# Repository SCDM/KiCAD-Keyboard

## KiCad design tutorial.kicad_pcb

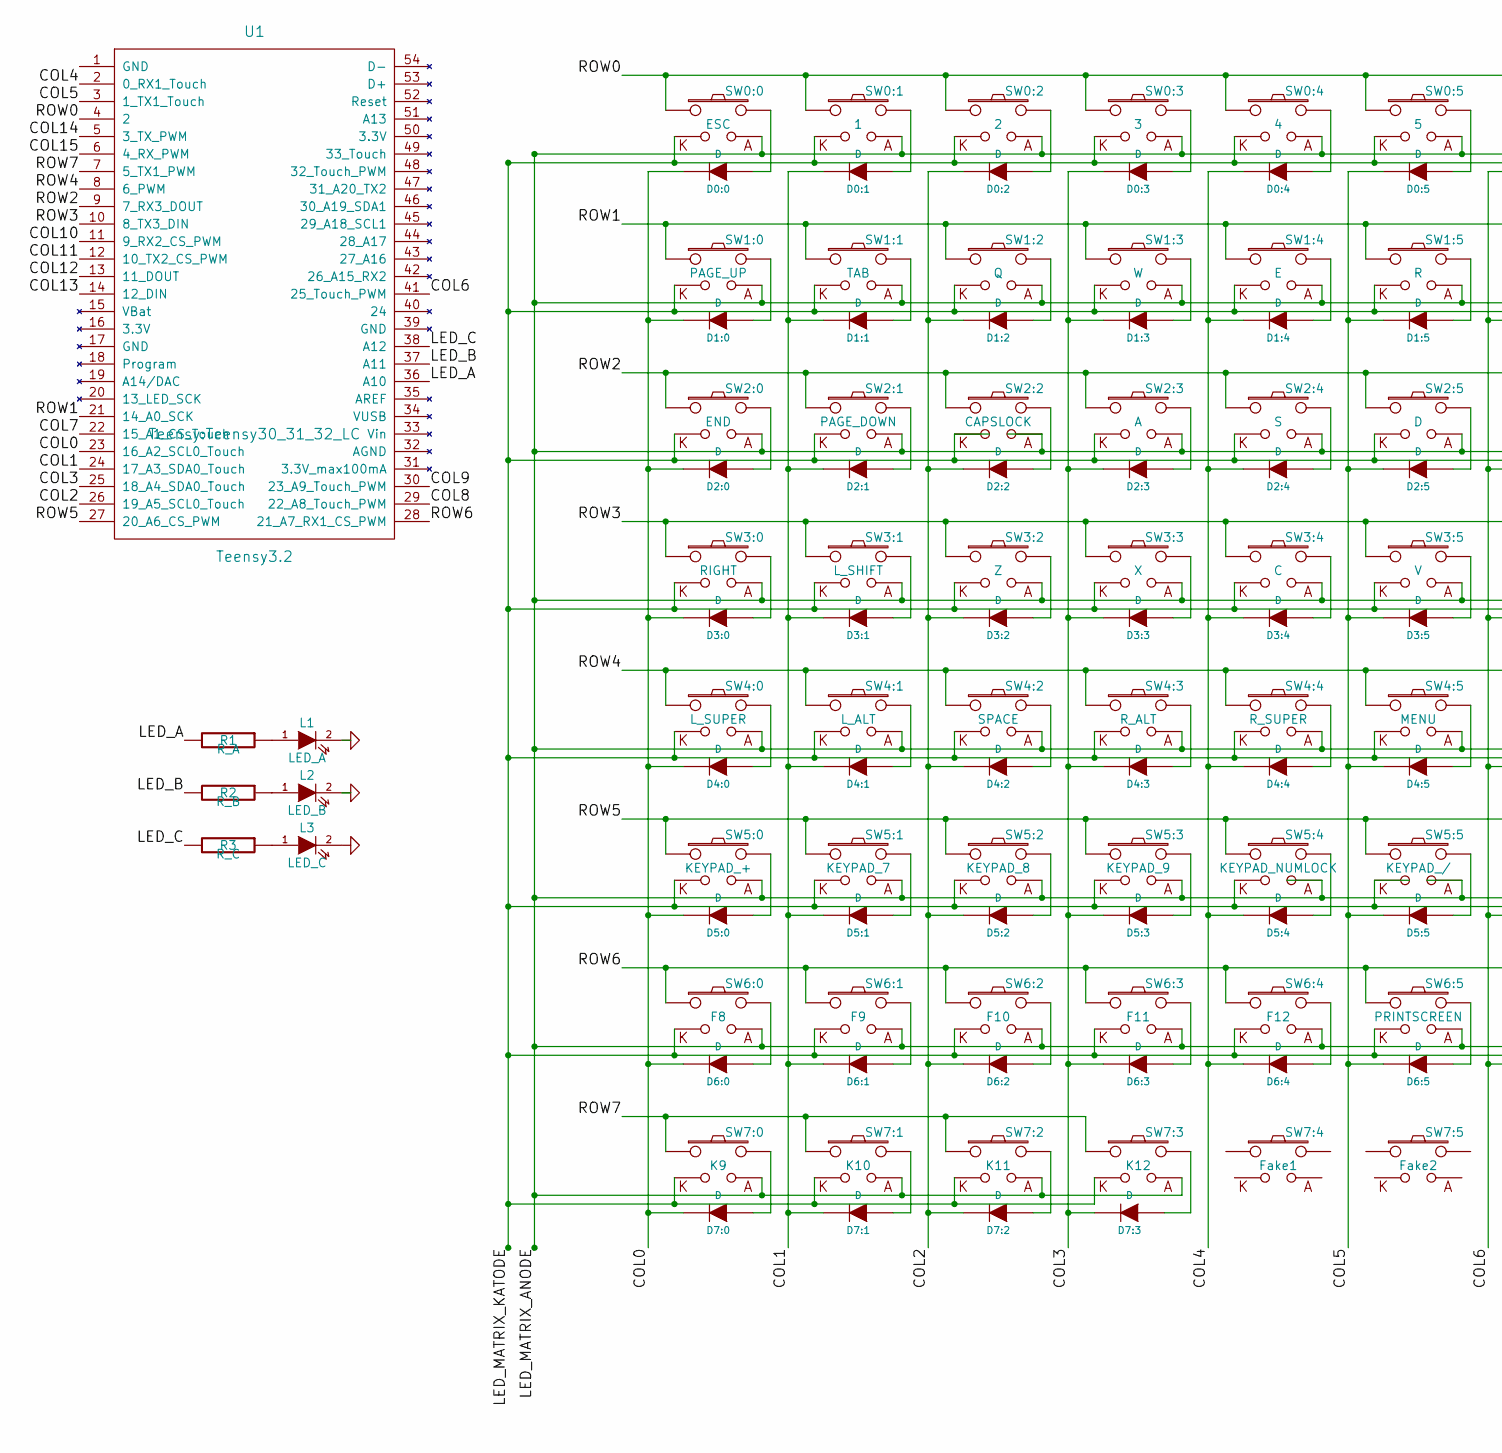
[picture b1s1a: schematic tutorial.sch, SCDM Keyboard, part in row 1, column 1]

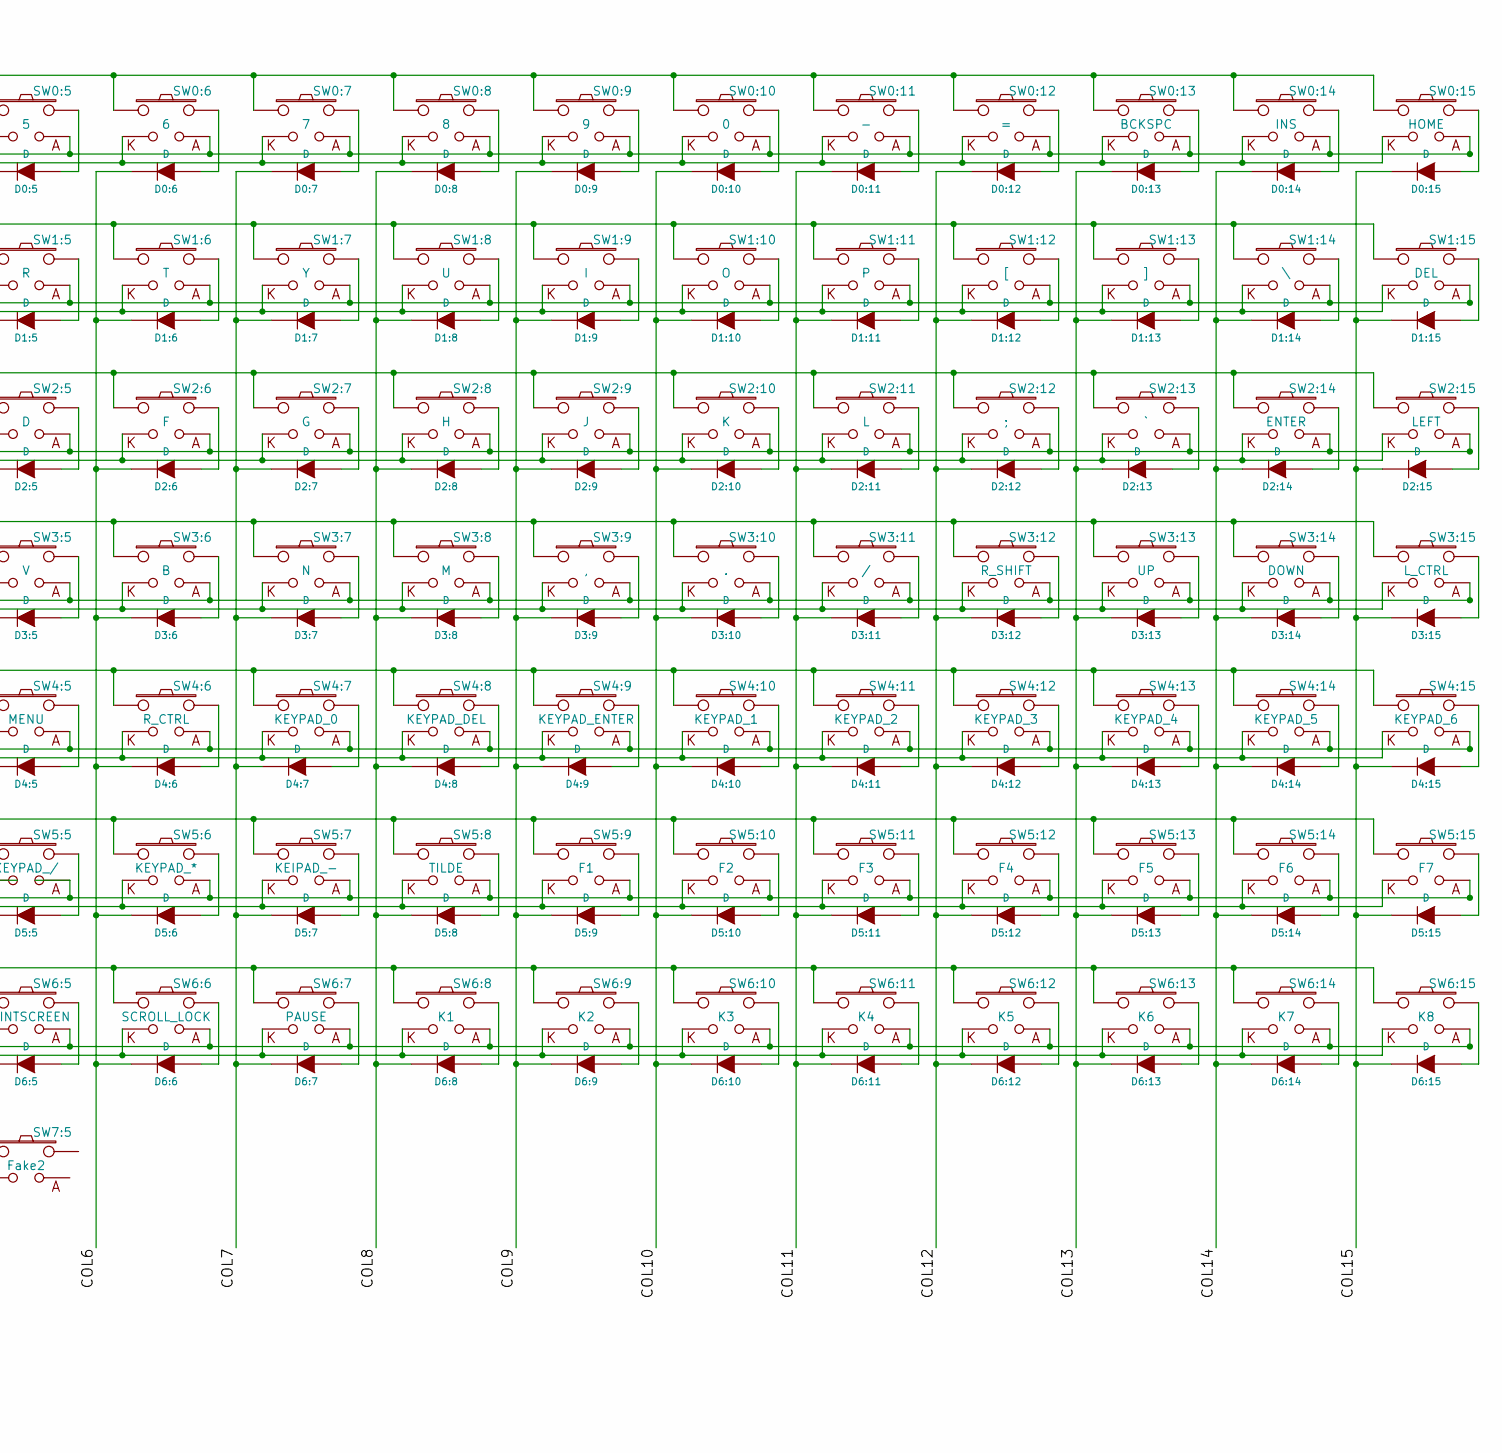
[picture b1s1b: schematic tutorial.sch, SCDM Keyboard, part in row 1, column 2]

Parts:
D0:0, D0:1, D0:2, D0:3, D0:4, D0:5, D0:6, D0:7, D0:8, D0:9, D0:10, D0:11, D0:12, D0:13, D0:14, D0:15, D1:0, D1:1, D1:2, D1:3, D1:4, D1:5, D1:6, D1:7, D1:8, D1:9, D1:10, D1:11, D1:12, D1:13, D1:14, D1:15, D2:0, D2:1, D2:2, D2:3, D2:4, D2:5, D2:6, D2:7, D2:8, D2:9, D2:10, D2:11, D2:12, D2:13, D2:14, D2:15, D3:0, D3:1, D3:2, D3:3, D3:4, D3:5, D3:6, D3:7, D3:8, D3:9, D3:10, D3:11, D3:12, D3:13, D3:14, D3:15, D4:0, D4:1, D4:2, D4:3, D4:4, D4:5, D4:6, D4:7, D4:8, D4:9, D4:10, D4:11, D4:12, D4:13, D4:14, D4:15, D5:0, D5:1, D5:2, D5:3, D5:4, D5:5, D5:6, D5:7, D5:8, D5:9, D5:10, D5:11, D5:12, D5:13, D5:14, D5:15, D6:0, D6:1, D6:2, D6:3, D6:4, D6:5, D6:6, D6:7, D6:8, D6:9, D6:10, D6:11, D6:12, D6:13, D6:14, D6:15, D7:0, D7:1, D7:2, D7:3: D; DIODE
L1: LED_A; CHERRY_MX_LED
L2: LED_B; CHERRY_MX_LED
L3: LED_C; CHERRY_MX_LED
R1: R_A; RESISTOR
R2: R_B; RESISTOR
R3: R_C; RESISTOR
SW0:0: ESC; CHERRY_PCB_100H_With_led2
SW0:1: 1; CHERRY_PCB_100H_With_led2
SW0:2: 2; CHERRY_PCB_100H_With_led2
SW0:3: 3; CHERRY_PCB_100H_With_led2
SW0:4: 4; CHERRY_PCB_100H_With_led2
SW0:5: 5; CHERRY_PCB_100H_With_led2
SW0:6: 6; CHERRY_PCB_100H_With_led2
SW0:7: 7; CHERRY_PCB_100H_With_led2
SW0:8: 8; CHERRY_PCB_100H_With_led2
SW0:9: 9; CHERRY_PCB_100H_With_led2
SW0:10: 0; CHERRY_PCB_100H_With_led2
SW0:11: -; CHERRY_PCB_100H_With_led2
SW0:12: =; CHERRY_PCB_100H_With_led2
SW0:13: BCKSPC; CHERRY_PCB_100H_With_led2
SW0:14: INS; CHERRY_PCB_100H_With_led2
SW0:15: HOME; CHERRY_PCB_100H_With_led2
SW1:0: PAGE_UP; CHERRY_PCB_100H_With_led2
SW1:1: TAB; CHERRY_PCB_100H_With_led2
SW1:2: Q; CHERRY_PCB_100H_With_led2
SW1:3: W; CHERRY_PCB_100H_With_led2
SW1:4: E; CHERRY_PCB_100H_With_led2
SW1:5: R; CHERRY_PCB_100H_With_led2
SW1:6: T; CHERRY_PCB_100H_With_led2
SW1:7: Y; CHERRY_PCB_100H_With_led2
SW1:8: U; CHERRY_PCB_100H_With_led2
SW1:9: I; CHERRY_PCB_100H_With_led2
SW1:10: O; CHERRY_PCB_100H_With_led2
SW1:11: P; CHERRY_PCB_100H_With_led2
SW1:12: [; CHERRY_PCB_100H_With_led2
SW1:13: ]; CHERRY_PCB_100H_With_led2
SW1:14: \\; CHERRY_PCB_100H_With_led2
SW1:15: DEL; CHERRY_PCB_100H_With_led2
SW2:0: END; CHERRY_PCB_100H_With_led2
SW2:1: PAGE_DOWN; CHERRY_PCB_100H_With_led2
SW2:2: CAPSLOCK; CHERRY_PCB_100H_With_led2
SW2:3: A; CHERRY_PCB_100H_With_led2
SW2:4: S; CHERRY_PCB_100H_With_led2
SW2:5: D; CHERRY_PCB_100H_With_led2
SW2:6: F; CHERRY_PCB_100H_With_led2
SW2:7: G; CHERRY_PCB_100H_With_led2
SW2:8: H; CHERRY_PCB_100H_With_led2
SW2:9: J; CHERRY_PCB_100H_With_led2
SW2:10: K; CHERRY_PCB_100H_With_led2
SW2:11: L; CHERRY_PCB_100H_With_led2
SW2:12: ;; CHERRY_PCB_100H_With_led2
SW2:13: `; CHERRY_PCB_100H_With_led2
SW2:14: ENTER; CHERRY_PCB_100H_With_led2
SW2:15: LEFT; CHERRY_PCB_100H_With_led2
SW3:0: RIGHT; CHERRY_PCB_100H_With_led2
SW3:1: L_SHIFT; CHERRY_PCB_100H_With_led2
SW3:2: Z; CHERRY_PCB_100H_With_led2
SW3:3: X; CHERRY_PCB_100H_With_led2
SW3:4: C; CHERRY_PCB_100H_With_led2
SW3:5: V; CHERRY_PCB_100H_With_led2
SW3:6: B; CHERRY_PCB_100H_With_led2
SW3:7: N; CHERRY_PCB_100H_With_led2
SW3:8: M; CHERRY_PCB_100H_With_led2
SW3:9: ,; CHERRY_PCB_100H_With_led2
SW3:10: .; CHERRY_PCB_100H_With_led2
SW3:11: /; CHERRY_PCB_100H_With_led2
SW3:12: R_SHIFT; CHERRY_PCB_100H_With_led2
SW3:13: UP; CHERRY_PCB_100H_With_led2
SW3:14: DOWN; CHERRY_PCB_100H_With_led2
SW3:15: L_CTRL; CHERRY_PCB_100H_With_led2
SW4:0: L_SUPER; CHERRY_PCB_100H_With_led2
SW4:1: L_ALT; CHERRY_PCB_100H_With_led2
SW4:2: SPACE; CHERRY_PCB_100H_With_led2
SW4:3: R_ALT; CHERRY_PCB_100H_With_led2
SW4:4: R_SUPER; CHERRY_PCB_100H_With_led2
SW4:5: MENU; CHERRY_PCB_100H_With_led2
SW4:6: R_CTRL; CHERRY_PCB_100H_With_led2
SW4:7: KEYPAD_0; CHERRY_PCB_100H_With_led2
SW4:8: KEYPAD_DEL; CHERRY_PCB_100H_With_led2
SW4:9: KEYPAD_ENTER; CHERRY_PCB_100H_With_led2
SW4:10: KEYPAD_1; CHERRY_PCB_100H_With_led2
SW4:11: KEYPAD_2; CHERRY_PCB_100H_With_led2
SW4:12: KEYPAD_3; CHERRY_PCB_100H_With_led2
SW4:13: KEYPAD_4; CHERRY_PCB_100H_With_led2
SW4:14: KEYPAD_5; CHERRY_PCB_100H_With_led2
SW4:15: KEYPAD_6; CHERRY_PCB_100H_With_led2
SW5:0: KEYPAD_+; CHERRY_PCB_100H_With_led2
SW5:1: KEYPAD_7; CHERRY_PCB_100H_With_led2
SW5:2: KEYPAD_8; CHERRY_PCB_100H_With_led2
SW5:3: KEYPAD_9; CHERRY_PCB_100H_With_led2
SW5:4: KEYPAD_NUMLOCK; CHERRY_PCB_100H_With_led2
SW5:5: KEYPAD_/; CHERRY_PCB_100H_With_led2
SW5:6: KEYPAD_*; CHERRY_PCB_100H_With_led2
SW5:7: KEIPAD_-; CHERRY_PCB_100H_With_led2
SW5:8: TILDE; CHERRY_PCB_100H_With_led2
SW5:9: F1; CHERRY_PCB_100H_With_led2
SW5:10: F2; CHERRY_PCB_100H_With_led2
SW5:11: F3; CHERRY_PCB_100H_With_led2
SW5:12: F4; CHERRY_PCB_100H_With_led2
SW5:13: F5; CHERRY_PCB_100H_With_led2
SW5:14: F6; CHERRY_PCB_100H_With_led2
SW5:15: F7; CHERRY_PCB_100H_With_led2
SW6:0: F8; CHERRY_PCB_100H_With_led2
SW6:1: F9; CHERRY_PCB_100H_With_led2
SW6:2: F10; CHERRY_PCB_100H_With_led2
SW6:3: F11; CHERRY_PCB_100H_With_led2
SW6:4: F12; CHERRY_PCB_100H_With_led2
SW6:5: PRINTSCREEN; CHERRY_PCB_100H_With_led2
SW6:6: SCROLL_LOCK; CHERRY_PCB_100H_With_led2
SW6:7: PAUSE; CHERRY_PCB_100H_With_led2
SW6:8: K1; CHERRY_PCB_100H_With_led2
SW6:9: K2; CHERRY_PCB_100H_With_led2
SW6:10: K3; CHERRY_PCB_100H_With_led2
SW6:11: K4; CHERRY_PCB_100H_With_led2
SW6:12: K5; CHERRY_PCB_100H_With_led2
SW6:13: K6; CHERRY_PCB_100H_With_led2
SW6:14: K7; CHERRY_PCB_100H_With_led2
SW6:15: K8; CHERRY_PCB_100H_With_led2
SW7:0: K9; CHERRY_PCB_100H_With_led2
SW7:1: K10; CHERRY_PCB_100H_With_led2
SW7:2: K11; CHERRY_PCB_100H_With_led2
SW7:3: K12; CHERRY_PCB_100H_With_led2
SW7:4: Fake1; CHERRY_PCB_100H_With_led2
SW7:5: Fake2; CHERRY_PCB_100H_With_led2
U1: Teensy3.2; Teensy30_31_32_LC

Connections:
/COL0: D0:0.2 (K), D1:0.2 (K), D2:0.2 (K), D3:0.2 (K), D4:0.2 (K), D5:0.2 (K), D6:0.2 (K), D7:0.2 (K), U1.23 (16_A2_SCL0_Touch)
/COL1: D0:1.2 (K), D1:1.2 (K), D2:1.2 (K), D3:1.2 (K), D4:1.2 (K), D5:1.2 (K), D6:1.2 (K), D7:1.2 (K), U1.24 (17_A3_SDA0_Touch)
/COL2: D0:2.2 (K), D1:2.2 (K), D2:2.2 (K), D3:2.2 (K), D4:2.2 (K), D5:2.2 (K), D6:2.2 (K), D7:2.2 (K), U1.26 (19_A5_SCL0_Touch)
/COL3: D0:3.2 (K), D1:3.2 (K), D2:3.2 (K), D3:3.2 (K), D4:3.2 (K), D5:3.2 (K), D6:3.2 (K), D7:3.2 (K), U1.25 (18_A4_SDA0_Touch)
/COL4: D0:4.2 (K), D1:4.2 (K), D2:4.2 (K), D3:4.2 (K), D4:4.2 (K), D5:4.2 (K), D6:4.2 (K), U1.2 (0_RX1_Touch)
/COL5: D0:5.2 (K), D1:5.2 (K), D2:5.2 (K), D3:5.2 (K), D4:5.2 (K), D5:5.2 (K), D6:5.2 (K), U1.3 (1_TX1_Touch)
/COL6: D0:6.2 (K), D1:6.2 (K), D2:6.2 (K), D3:6.2 (K), D4:6.2 (K), D5:6.2 (K), D6:6.2 (K), U1.41 (25_Touch_PWM)
/COL7: D0:7.2 (K), D1:7.2 (K), D2:7.2 (K), D3:7.2 (K), D4:7.2 (K), D5:7.2 (K), D6:7.2 (K), U1.22 (15_A1_CS_Touch)
/COL8: D0:8.2 (K), D1:8.2 (K), D2:8.2 (K), D3:8.2 (K), D4:8.2 (K), D5:8.2 (K), D6:8.2 (K), U1.29 (22_A8_Touch_PWM)
/COL9: D0:9.2 (K), D1:9.2 (K), D2:9.2 (K), D3:9.2 (K), D4:9.2 (K), D5:9.2 (K), D6:9.2 (K), U1.30 (23_A9_Touch_PWM)
/COL10: D0:10.2 (K), D1:10.2 (K), D2:10.2 (K), D3:10.2 (K), D4:10.2 (K), D5:10.2 (K), D6:10.2 (K), U1.11 (9_RX2_CS_PWM)
/COL11: D0:11.2 (K), D1:11.2 (K), D2:11.2 (K), D3:11.2 (K), D4:11.2 (K), D5:11.2 (K), D6:11.2 (K), U1.12 (10_TX2_CS_PWM)
/COL12: D0:12.2 (K), D1:12.2 (K), D2:12.2 (K), D3:12.2 (K), D4:12.2 (K), D5:12.2 (K), D6:12.2 (K), U1.13 (11_DOUT)
/COL13: D0:13.2 (K), D1:13.2 (K), D2:13.2 (K), D3:13.2 (K), D4:13.2 (K), D5:13.2 (K), D6:13.2 (K), U1.14 (12_DIN)
/COL14: D0:14.2 (K), D1:14.2 (K), D2:14.2 (K), D3:14.2 (K), D4:14.2 (K), D5:14.2 (K), D6:14.2 (K), U1.5 (3_TX_PWM)
/COL15: D0:15.2 (K), D1:15.2 (K), D2:15.2 (K), D3:15.2 (K), D4:15.2 (K), D5:15.2 (K), D6:15.2 (K), U1.6 (4_RX_PWM)
/LED_A: R1.2, U1.36 (A10)
/LED_B: R2.2, U1.37 (A11)
/LED_C: R3.2, U1.38 (A12)
/ROW0: SW0:0.1, SW0:1.1, SW0:2.1, SW0:3.1, SW0:4.1, SW0:5.1, SW0:6.1, SW0:7.1, SW0:8.1, SW0:9.1, SW0:10.1, SW0:11.1, SW0:12.1, SW0:13.1, SW0:14.1, SW0:15.1, U1.4 (2)
/ROW1: SW1:0.1, SW1:1.1, SW1:2.1, SW1:3.1, SW1:4.1, SW1:5.1, SW1:6.1, SW1:7.1, SW1:8.1, SW1:9.1, SW1:10.1, SW1:11.1, SW1:12.1, SW1:13.1, SW1:14.1, SW1:15.1, U1.21 (14_A0_SCK)
/ROW2: SW2:0.1, SW2:1.1, SW2:2.1, SW2:3.1, SW2:4.1, SW2:5.1, SW2:6.1, SW2:7.1, SW2:8.1, SW2:9.1, SW2:10.1, SW2:11.1, SW2:12.1, SW2:13.1, SW2:14.1, SW2:15.1, U1.9 (7_RX3_DOUT)
/ROW3: SW3:0.1, SW3:1.1, SW3:2.1, SW3:3.1, SW3:4.1, SW3:5.1, SW3:6.1, SW3:7.1, SW3:8.1, SW3:9.1, SW3:10.1, SW3:11.1, SW3:12.1, SW3:13.1, SW3:14.1, SW3:15.1, U1.10 (8_TX3_DIN)
/ROW4: SW4:0.1, SW4:1.1, SW4:2.1, SW4:3.1, SW4:4.1, SW4:5.1, SW4:6.1, SW4:7.1, SW4:8.1, SW4:9.1, SW4:10.1, SW4:11.1, SW4:12.1, SW4:13.1, SW4:14.1, SW4:15.1, U1.8 (6_PWM)
/ROW5: SW5:0.1, SW5:1.1, SW5:2.1, SW5:3.1, SW5:4.1, SW5:5.1, SW5:6.1, SW5:7.1, SW5:8.1, SW5:9.1, SW5:10.1, SW5:11.1, SW5:12.1, SW5:13.1, SW5:14.1, SW5:15.1, U1.27 (20_A6_CS_PWM)
/ROW6: SW6:0.1, SW6:1.1, SW6:2.1, SW6:3.1, SW6:4.1, SW6:5.1, SW6:6.1, SW6:7.1, SW6:8.1, SW6:9.1, SW6:10.1, SW6:11.1, SW6:12.1, SW6:13.1, SW6:14.1, SW6:15.1, U1.28 (21_A7_RX1_CS_PWM)
/ROW7: SW7:0.1, SW7:1.1, SW7:2.1, SW7:3.1, U1.7 (5_TX1_PWM)
GND: L1.2 (K), L2.2 (K), L3.2 (K)
unnamed: D0:0.1 (A), SW0:0.2
unnamed: D0:1.1 (A), SW0:1.2
unnamed: D0:2.1 (A), SW0:2.2
unnamed: D0:3.1 (A), SW0:3.2
unnamed: D0:4.1 (A), SW0:4.2
unnamed: D0:5.1 (A), SW0:5.2
unnamed: D0:6.1 (A), SW0:6.2
unnamed: D0:7.1 (A), SW0:7.2
unnamed: D0:8.1 (A), SW0:8.2
unnamed: D0:9.1 (A), SW0:9.2
unnamed: D0:10.1 (A), SW0:10.2
unnamed: D0:11.1 (A), SW0:11.2
unnamed: D0:12.1 (A), SW0:12.2
unnamed: D0:13.1 (A), SW0:13.2
unnamed: D0:14.1 (A), SW0:14.2
unnamed: D0:15.1 (A), SW0:15.2
unnamed: D1:0.1 (A), SW1:0.2
unnamed: D1:1.1 (A), SW1:1.2
unnamed: D1:2.1 (A), SW1:2.2
unnamed: D1:3.1 (A), SW1:3.2
unnamed: D1:4.1 (A), SW1:4.2
unnamed: D1:5.1 (A), SW1:5.2
unnamed: D1:6.1 (A), SW1:6.2
unnamed: D1:7.1 (A), SW1:7.2
unnamed: D1:8.1 (A), SW1:8.2
unnamed: D1:9.1 (A), SW1:9.2
unnamed: D1:10.1 (A), SW1:10.2
unnamed: D1:11.1 (A), SW1:11.2
unnamed: D1:12.1 (A), SW1:12.2
unnamed: D1:13.1 (A), SW1:13.2
unnamed: D1:14.1 (A), SW1:14.2
unnamed: D1:15.1 (A), SW1:15.2
unnamed: D2:0.1 (A), SW2:0.2
unnamed: D2:1.1 (A), SW2:1.2
unnamed: D2:2.1 (A), SW2:2.2
unnamed: D2:3.1 (A), SW2:3.2
unnamed: D2:4.1 (A), SW2:4.2
unnamed: D2:5.1 (A), SW2:5.2
unnamed: D2:6.1 (A), SW2:6.2
unnamed: D2:7.1 (A), SW2:7.2
unnamed: D2:8.1 (A), SW2:8.2
unnamed: D2:9.1 (A), SW2:9.2
unnamed: D2:10.1 (A), SW2:10.2
unnamed: D2:11.1 (A), SW2:11.2
unnamed: D2:12.1 (A), SW2:12.2
unnamed: D2:13.1 (A), SW2:13.2
unnamed: D2:14.1 (A), SW2:14.2
unnamed: D2:15.1 (A), SW2:15.2
unnamed: D3:0.1 (A), SW3:0.2
unnamed: D3:1.1 (A), SW3:1.2
unnamed: D3:2.1 (A), SW3:2.2
unnamed: D3:3.1 (A), SW3:3.2
unnamed: D3:4.1 (A), SW3:4.2
unnamed: D3:5.1 (A), SW3:5.2
unnamed: D3:6.1 (A), SW3:6.2
unnamed: D3:7.1 (A), SW3:7.2
unnamed: D3:8.1 (A), SW3:8.2
unnamed: D3:9.1 (A), SW3:9.2
unnamed: D3:10.1 (A), SW3:10.2
unnamed: D3:11.1 (A), SW3:11.2
unnamed: D3:12.1 (A), SW3:12.2
unnamed: D3:13.1 (A), SW3:13.2
unnamed: D3:14.1 (A), SW3:14.2
unnamed: D3:15.1 (A), SW3:15.2
unnamed: D4:0.1 (A), SW4:0.2
unnamed: D4:1.1 (A), SW4:1.2
unnamed: D4:2.1 (A), SW4:2.2
unnamed: D4:3.1 (A), SW4:3.2
unnamed: D4:4.1 (A), SW4:4.2
unnamed: D4:5.1 (A), SW4:5.2
unnamed: D4:6.1 (A), SW4:6.2
unnamed: D4:7.1 (A), SW4:7.2
unnamed: D4:8.1 (A), SW4:8.2
unnamed: D4:9.1 (A), SW4:9.2
unnamed: D4:10.1 (A), SW4:10.2
unnamed: D4:11.1 (A), SW4:11.2
unnamed: D4:12.1 (A), SW4:12.2
unnamed: D4:13.1 (A), SW4:13.2
unnamed: D4:14.1 (A), SW4:14.2
unnamed: D4:15.1 (A), SW4:15.2
unnamed: D5:0.1 (A), SW5:0.2
unnamed: D5:1.1 (A), SW5:1.2
unnamed: D5:2.1 (A), SW5:2.2
unnamed: D5:3.1 (A), SW5:3.2
unnamed: D5:4.1 (A), SW5:4.2
unnamed: D5:5.1 (A), SW5:5.2
unnamed: D5:6.1 (A), SW5:6.2
unnamed: D5:7.1 (A), SW5:7.2
unnamed: D5:8.1 (A), SW5:8.2
unnamed: D5:9.1 (A), SW5:9.2
unnamed: D5:10.1 (A), SW5:10.2
unnamed: D5:11.1 (A), SW5:11.2
unnamed: D5:12.1 (A), SW5:12.2
unnamed: D5:13.1 (A), SW5:13.2
unnamed: D5:14.1 (A), SW5:14.2
unnamed: D5:15.1 (A), SW5:15.2
unnamed: D6:0.1 (A), SW6:0.2
unnamed: D6:1.1 (A), SW6:1.2
unnamed: D6:2.1 (A), SW6:2.2
unnamed: D6:3.1 (A), SW6:3.2
unnamed: D6:4.1 (A), SW6:4.2
unnamed: D6:5.1 (A), SW6:5.2
unnamed: D6:6.1 (A), SW6:6.2
unnamed: D6:7.1 (A), SW6:7.2
unnamed: D6:8.1 (A), SW6:8.2
unnamed: D6:9.1 (A), SW6:9.2
unnamed: D6:10.1 (A), SW6:10.2
unnamed: D6:11.1 (A), SW6:11.2
unnamed: D6:12.1 (A), SW6:12.2
unnamed: D6:13.1 (A), SW6:13.2
unnamed: D6:14.1 (A), SW6:14.2
unnamed: D6:15.1 (A), SW6:15.2
unnamed: D7:0.1 (A), SW7:0.2
unnamed: D7:1.1 (A), SW7:1.2
unnamed: D7:2.1 (A), SW7:2.2
unnamed: D7:3.1 (A), SW7:3.2
unnamed: L1.1 (A), R1.1
unnamed: L2.1 (A), R2.1
unnamed: L3.1 (A), R3.1

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
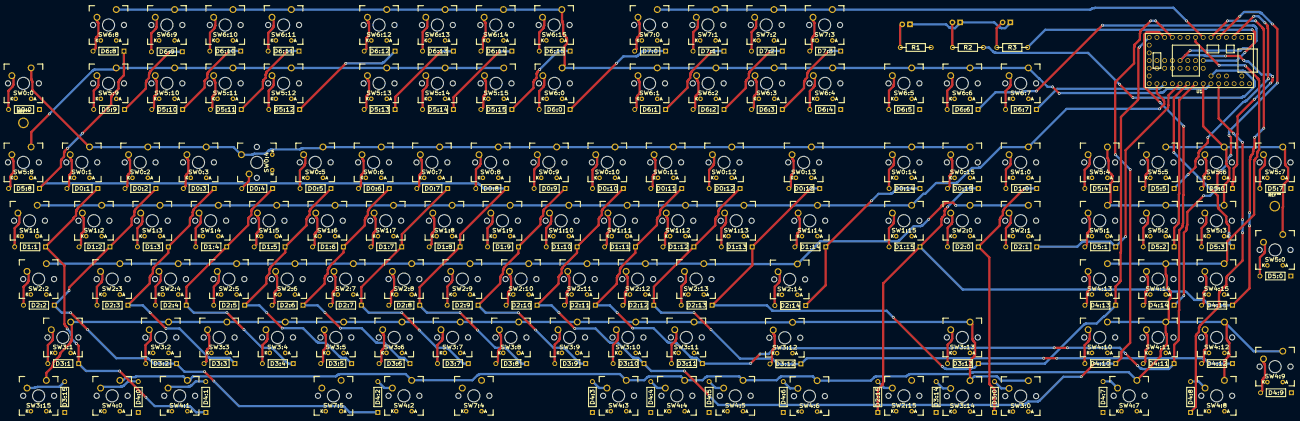
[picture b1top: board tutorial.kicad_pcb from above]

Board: 2 copper layers, 241 parts (0 on the bottom side), 147 nets.

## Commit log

2016-12-16 second commit
2016-12-22 3° commit
2017-01-04 another little step
2017-01-04 sbroglio terminato
2017-05-16 4o step
2017-05-16 5o step
2017-05-16 5o step con aggiunta del taglio
